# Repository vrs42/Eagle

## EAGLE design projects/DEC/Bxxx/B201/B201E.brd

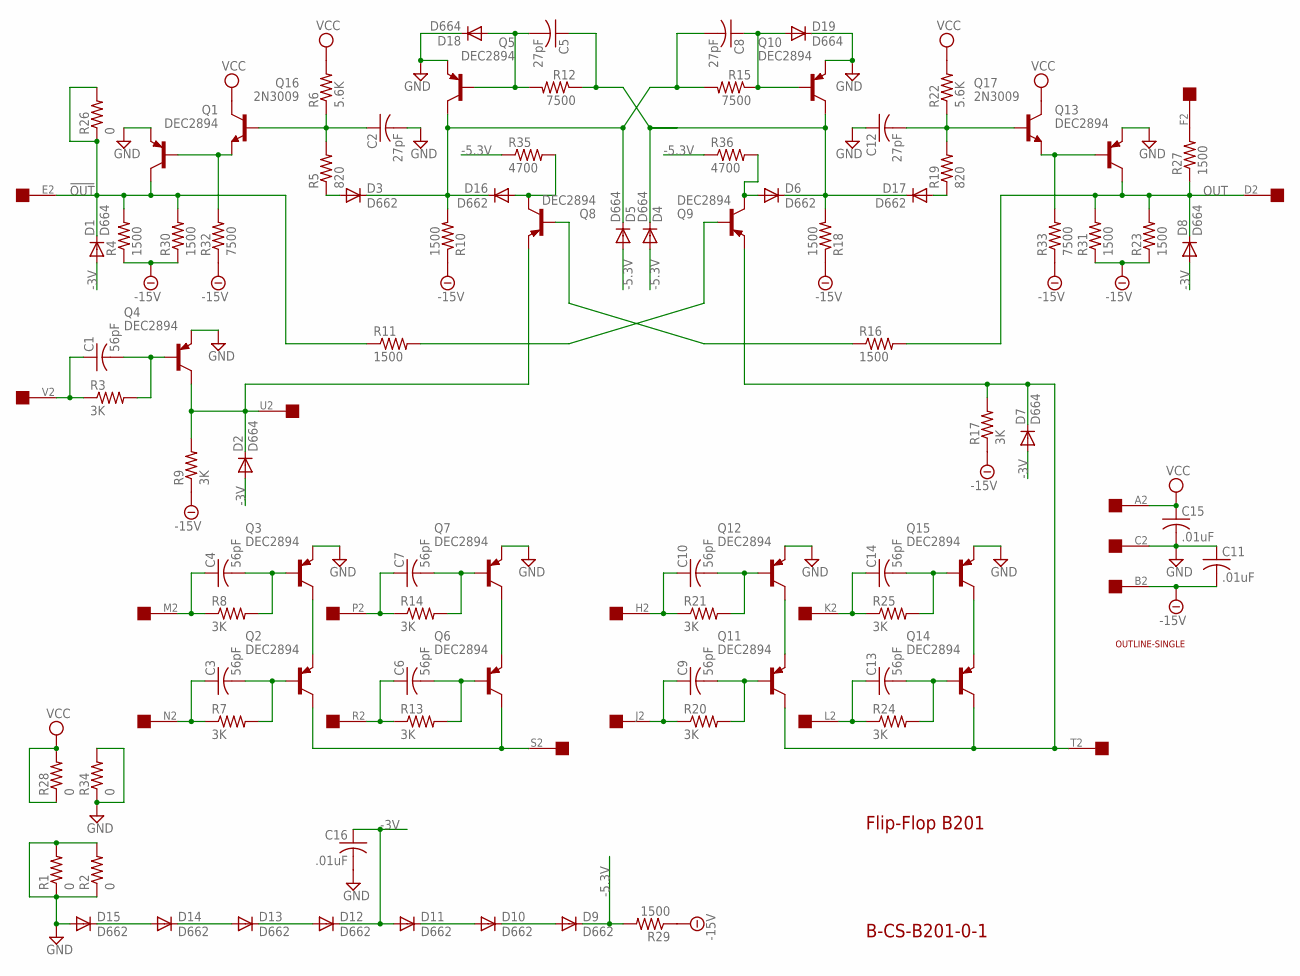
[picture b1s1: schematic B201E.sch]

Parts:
C1, C3, C4, C6, C7, C9, C10, C13, C14: 56pF; C063-025X075
C2, C5, C8, C12: 27pF; C063-025X075
C11, C15, C16: .01uF; C063-025X075
D1, D2, D4, D5, D7, D8, D18, D19: D664; DO35-10
D3, D6, D9, D10, D11, D12, D13, D14, D15, D16, D17: D662; DO35-10
Q1, Q2, Q3, Q4, Q5, Q6, Q7, Q8, Q9, Q10, Q11, Q12, Q13, Q14, Q15: DEC2894; TO5
Q16, Q17: 2N3009; TO5
R1, R2, R26, R28, R34: 0; 0207/10
R3, R7, R8, R9, R13, R14, R17, R20, R21, R24, R25: 3K; 0207/10
R4, R10, R11, R16, R18, R23, R27, R29, R30, R31: 1500; 0207/10
R5, R19: 820; 0207/10
R6, R22: 5.6K; 0207/10
R12, R15, R32, R33: 7500; 0207/10
R35, R36: 4700; 0207/10
U$1: OUTLINE-SINGLE; SINGLE
U$2: EDGE-1; EDGE-CON1

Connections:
!OUT: D1.C, Q1.3 (C), R4.2, R11.1, R26.1, R26.2, R30.2, U$2.E2
-3V: C16.1, D1.A, D2.A, D7.A, D8.A, D11.A, D12.C
-5.3V: D4.A, D5.A, D9.C, R29.2, R35.1, R36.1
-15V: C11.2, R4.1, R9.1, R10.1, R17.1, R18.1, R23.1, R29.1, R30.1, R31.1, R32.1, R33.1, U$2.B2
-.75V: D14.A, D15.C
GND: C2.2, C11.1, C12.1, C15.2, C16.2, D15.A, D18.C, D19.C, Q1.1 (E), Q3.1 (E), Q4.1 (E), Q5.1 (E), Q7.1 (E), Q10.1 (E), Q12.1 (E), Q13.1 (E), Q15.1 (E), R1.1, R1.2, R2.1, R2.2, R34.1, R34.2, U$2.C2
unnamed: C4.1, R8.1, U$2.M2
unnamed: C4.2, Q3.2 (B), R8.2
unnamed: C3.1, R7.1, U$2.N2
unnamed: C3.2, Q2.2 (B), R7.2
unnamed: Q2.1 (E), Q3.3 (C)
unnamed: Q2.3 (C), Q6.3 (C), U$2.S2
unnamed: C7.1, R14.1, U$2.P2
unnamed: C7.2, Q7.2 (B), R14.2
unnamed: C6.1, R13.1, U$2.R2
unnamed: C6.2, Q6.2 (B), R13.2
unnamed: Q6.1 (E), Q7.3 (C)
unnamed: C1.1, R3.1, U$2.V2
unnamed: C10.1, R21.1, U$2.H2
unnamed: C10.2, Q12.2 (B), R21.2
unnamed: C9.1, R20.1, U$2.J2
unnamed: C9.2, Q11.2 (B), R20.2
unnamed: Q11.1 (E), Q12.3 (C)
unnamed: D7.C, Q9.1 (E), Q11.3 (C), Q14.3 (C), R17.2, U$2.T2
unnamed: C14.1, R25.1, U$2.K2
unnamed: C14.2, Q15.2 (B), R25.2
unnamed: C13.1, R24.1, U$2.L2
unnamed: C13.2, Q14.2 (B), R24.2
unnamed: Q14.1 (E), Q15.3 (C)
unnamed: C1.2, Q4.2 (B), R3.2
unnamed: R27.2, U$2.F2
unnamed: D2.C, Q4.3 (C), Q8.1 (E), R9.2, U$2.U2
unnamed: Q1.2 (B), Q16.1 (E), R32.2
unnamed: D9.A, D10.C
unnamed: D10.A, D11.C
unnamed: C2.1, Q16.2 (B), R5.2, R6.1
unnamed: D13.A, D14.C
unnamed: D12.A, D13.C
unnamed: D3.A, R5.1
unnamed: C5.1, D4.C, D6.C, D17.C, Q10.3 (C), R12.1, R18.2
unnamed: Q8.2 (B), R16.1
unnamed: C8.1, D19.A, Q10.2 (B), R15.1
unnamed: C8.2, D3.C, D5.C, D16.C, Q5.3 (C), R10.2, R15.2
unnamed: Q9.2 (B), R11.2
unnamed: C5.2, D18.A, Q5.2 (B), R12.2
unnamed: D16.A, Q8.3 (C), R35.2
unnamed: C12.2, Q17.2 (B), R19.2, R22.1
unnamed: D17.A, R19.1
unnamed: Q13.2 (B), Q17.1 (E), R33.2
unnamed: D6.A, Q9.3 (C), R36.2
OUT: D8.C, Q13.3 (C), R16.2, R23.2, R27.1, R31.2, U$2.D2
VCC: C15.1, Q16.3 (C), Q17.3 (C), R6.2, R22.2, R28.1, R28.2, U$2.A2

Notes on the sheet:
Flip-Flop B201
B-CS-B201-0-1

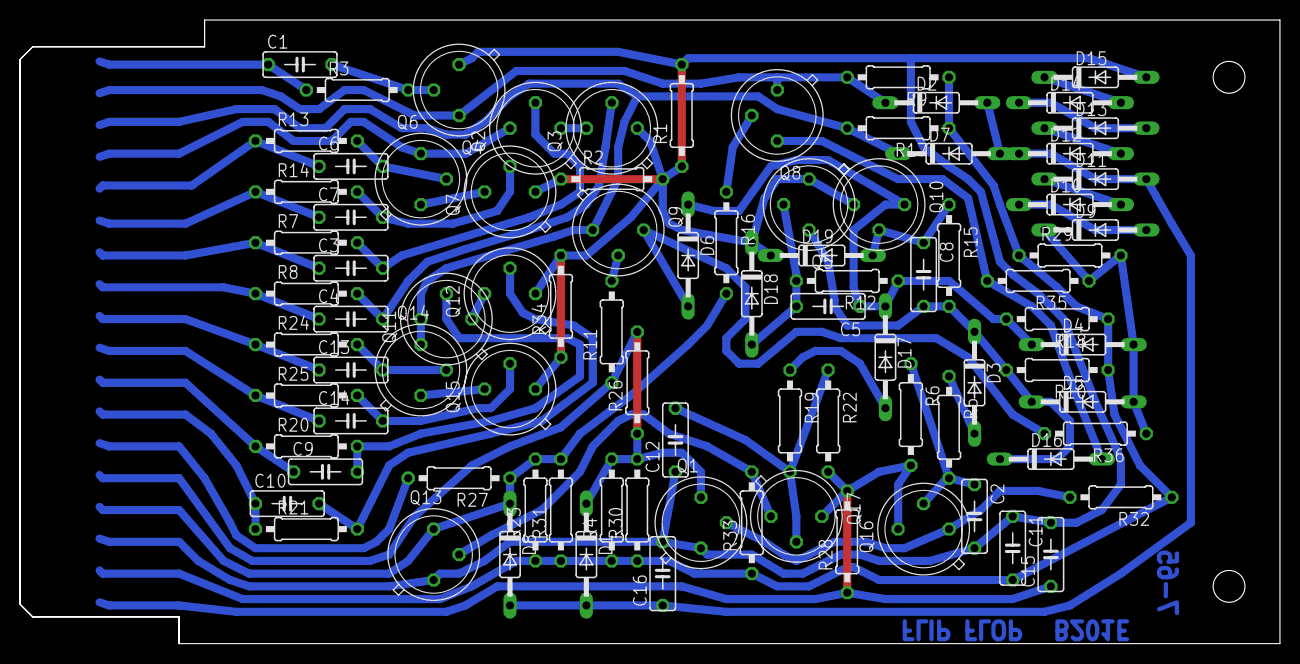
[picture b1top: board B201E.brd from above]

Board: 2 copper layers, 125.7 x 62.2 mm, 90 parts (0 on the bottom side), 52 nets.

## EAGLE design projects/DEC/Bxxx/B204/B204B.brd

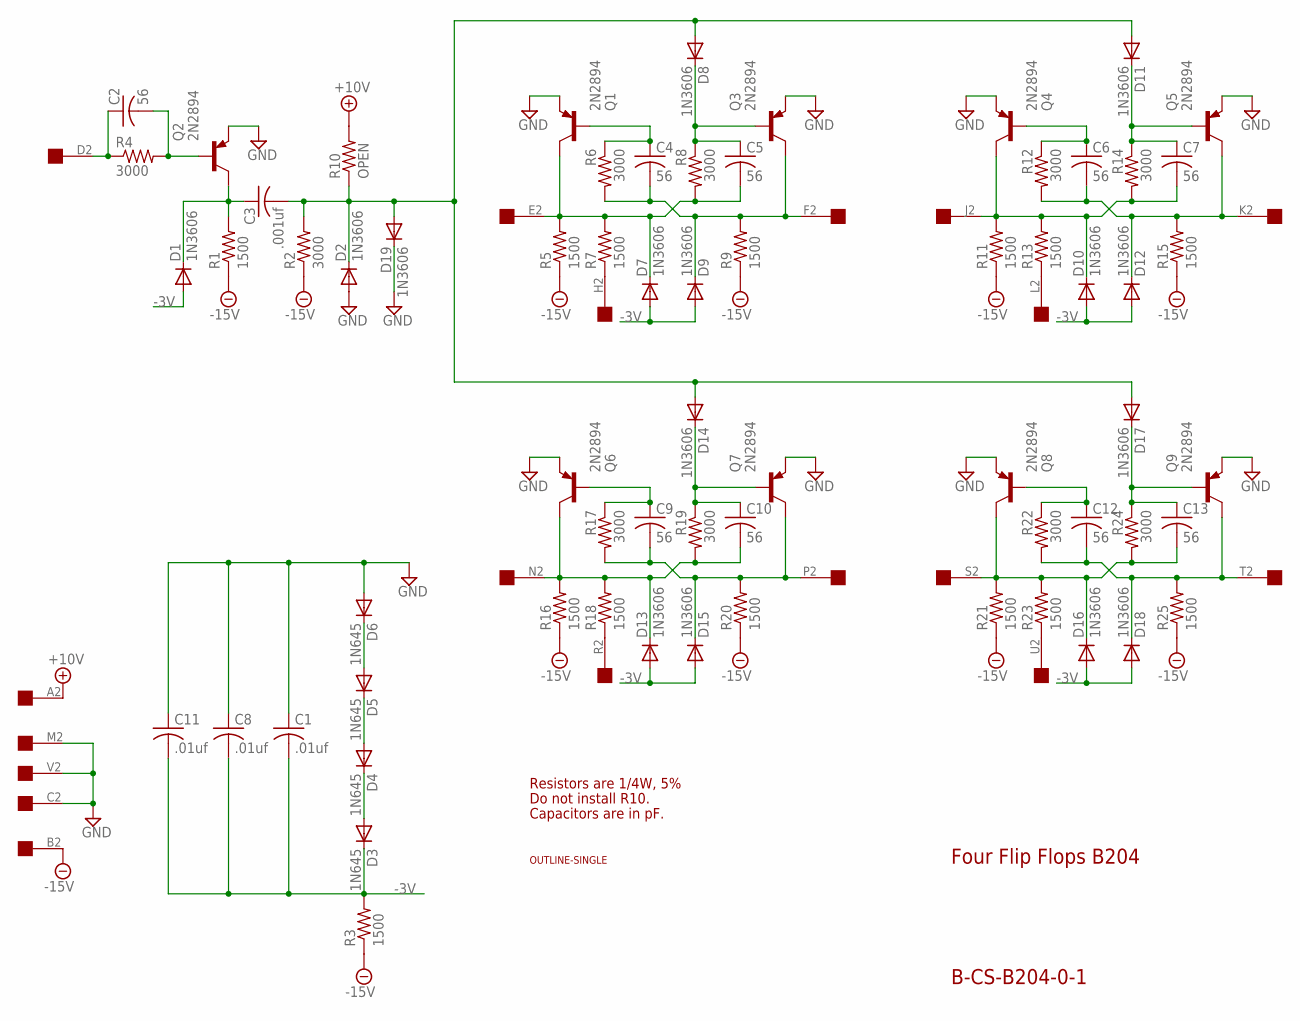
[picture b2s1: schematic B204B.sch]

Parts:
C1, C8, C11: .01uf; C050-025X075
C2, C4, C5, C6, C7, C9, C10, C12, C13: 56; C075-032X103
C3: .001uf; C050-025X075
D1, D2, D7, D8, D9, D10, D11, D12, D13, D14, D15, D16, D17, D18, D19: 1N3606; DO35-10
D3, D4, D5, D6: 1N645; DO35-10
Q1, Q2, Q3, Q4, Q5, Q6, Q7, Q8, Q9: 2N2894; TO39
R1, R3, R5, R7, R9, R11, R13, R15, R16, R18, R20, R21, R23, R25: 1500; 0207/10
R2, R4, R6, R8, R12, R14, R17, R19, R22, R24: 3000; 0207/10
R10: OPEN; 0207/10
U$1: OUTLINE-SINGLE; SINGLE
U$2: EDGE-1; EDGE-CON1

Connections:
+10V: R10.2, U$2.A2
-3V: C1.2, C8.2, C11.2, D1.A, D3.C, D7.A, D9.A, D10.A, D12.A, D13.A, D15.A, D16.A, D18.A, R3.2
-15V: R1.1, R2.1, R3.1, R5.1, R9.1, R11.1, R15.1, R16.1, R20.1, R21.1, R25.1, U$2.B2
GND: C1.1, C8.1, C11.1, D2.A, D6.A, D19.C, Q1.1 (E), Q2.1 (E), Q3.1 (E), Q4.1 (E), Q5.1 (E), Q6.1 (E), Q7.1 (E), Q8.1 (E), Q9.1 (E), U$2.C2, U$2.M2, U$2.V2
unnamed: C2.1, R4.1, U$2.D2
unnamed: C4.1, Q1.2 (B), R6.1
unnamed: C2.2, Q2.2 (B), R4.2
unnamed: C3.1, D1.C, Q2.3 (C), R1.2
unnamed: R7.1, U$2.H2
unnamed: C5.2, D7.C, Q1.3 (C), R5.2, R7.2, R8.2, U$2.E2
unnamed: C5.1, D8.C, Q3.2 (B), R8.1
unnamed: C3.2, D2.C, D8.A, D11.A, D14.A, D17.A, D19.A, R2.2, R10.1
unnamed: C4.2, D9.C, Q3.3 (C), R6.2, R9.2, U$2.F2
unnamed: R13.1, U$2.L2
unnamed: C6.1, Q4.2 (B), R12.1
unnamed: D4.A, D5.C
unnamed: C7.1, D11.C, Q5.2 (B), R14.1
unnamed: C7.2, D10.C, Q4.3 (C), R11.2, R13.2, R14.2, U$2.J2
unnamed: D3.A, D4.C
unnamed: C6.2, D12.C, Q5.3 (C), R12.2, R15.2, U$2.K2
unnamed: R18.1, U$2.R2
unnamed: C9.1, Q6.2 (B), R17.1
unnamed: C10.1, D14.C, Q7.2 (B), R19.1
unnamed: C10.2, D13.C, Q6.3 (C), R16.2, R18.2, R19.2, U$2.N2
unnamed: C9.2, D15.C, Q7.3 (C), R17.2, R20.2, U$2.P2
unnamed: R23.1, U$2.U2
unnamed: C12.1, Q8.2 (B), R22.1
unnamed: C13.1, D17.C, Q9.2 (B), R24.1
unnamed: C13.2, D16.C, Q8.3 (C), R21.2, R23.2, R24.2, U$2.S2
unnamed: C12.2, D18.C, Q9.3 (C), R22.2, R25.2, U$2.T2
unnamed: D5.A, D6.C

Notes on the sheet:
Four Flip Flops B204
B-CS-B204-0-1
Resistors are 1/4W, 5%
Do not install R10.
Capacitors are in pF.

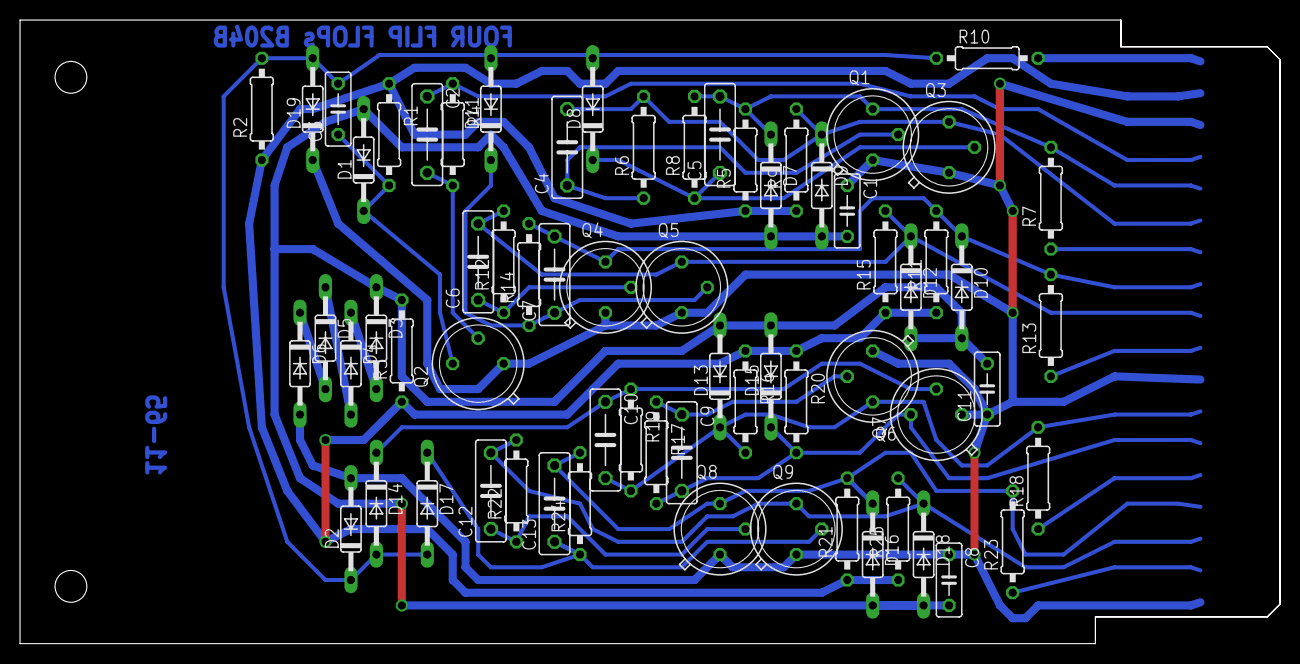
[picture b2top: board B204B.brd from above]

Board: 2 copper layers, 125.7 x 62.2 mm, 68 parts (0 on the bottom side), 31 nets.

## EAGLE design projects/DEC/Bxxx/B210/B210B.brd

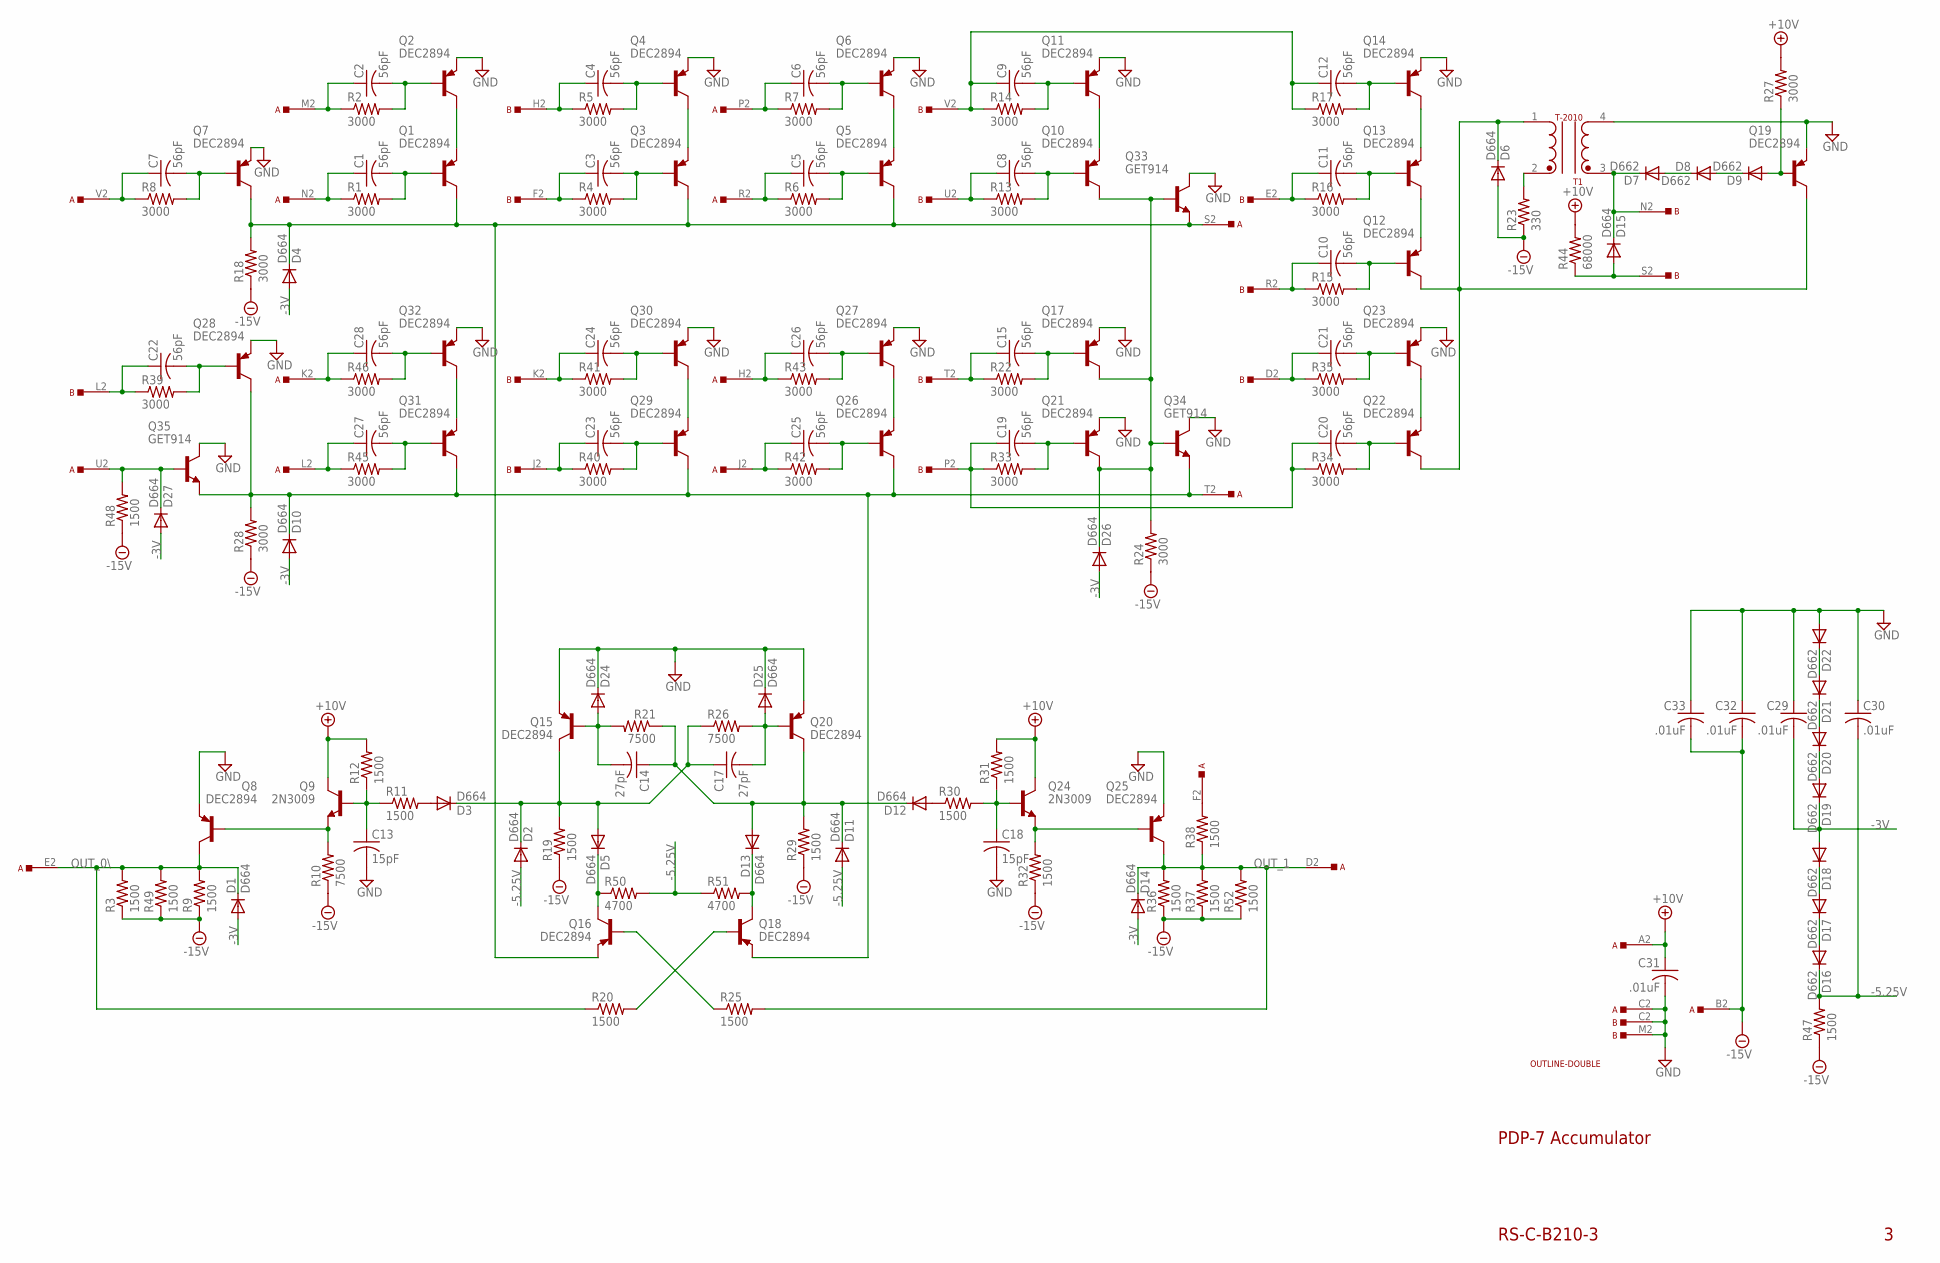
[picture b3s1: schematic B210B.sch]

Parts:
A: SS-TOP; EDGE-CON1
B: SS-TOP; EDGE-CON1
C1, C2, C3, C4, C5, C6, C7, C8, C9, C10, C11, C12, C15, C19, C20, C21, C22, C23, C24, C25, C26, C27, C28: 56pF; C063-025X075
C13, C18: 15pF; C063-025X075
C14, C17: 27pF; C063-025X075
C29, C30, C31, C32, C33: .01uF; C063-025X075
D1, D2, D3, D4, D5, D6, D10, D11, D12, D13, D14, D15, D24, D25, D26, D27: D664; DO35-10
D7, D8, D9, D16, D17, D18, D19, D20, D21, D22: D662; DO35-10
Q1, Q2, Q3, Q4, Q5, Q6, Q7, Q8, Q10, Q11, Q12, Q13, Q14, Q15, Q16, Q17, Q18, Q19, Q20, Q21, Q22, Q23, Q25, Q26, Q27, Q28, Q29, Q30, Q31, Q32: DEC2894; TO5
Q9, Q24: 2N3009; TO5
Q33, Q34, Q35: GET914; TO5
R1, R2, R4, R5, R6, R7, R8, R13, R14, R15, R16, R17, R18, R22, R24, R27, R28, R33, R34, R35, R39, R40, R41, R42, R43, R45, R46: 3000; 0207/10
R3, R9, R11, R12, R19, R20, R25, R29, R30, R31, R32, R36, R37, R38, R47, R48, R49, R52: 1500; 0207/10
R10, R21, R26: 7500; 0207/10
R23: 330; 0207/10
R44: 68000; 0207/10
R50, R51: 4700; 0207/10
T1: T-2010; TRANSFORMER2
U$1: OUTLINE-DOUBLE; DOUBLE

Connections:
+10V: A.A2, C31.1, Q9.3 (C), Q24.3 (C), R12.2, R27.2, R31.2, R44.2
-3V: C29.2, D1.A, D4.A, D10.A, D14.A, D18.A, D19.C, D26.A, D27.A
-5.25V: C30.2, D2.A, D11.A, D16.C, R47.2, R50.2, R51.1
-15V: A.B2, C32.2, C33.2, D6.A, R3.1, R9.1, R10.1, R18.1, R19.1, R23.1, R24.1, R28.1, R29.1, R32.1, R36.1, R37.1, R47.1, R48.1, R49.1, R52.1
GND: A.C2, B.C2, B.M2, C13.2, C18.2, C29.1, C30.1, C31.2, C32.1, C33.1, D22.A, D24.C, D25.C, Q2.1 (E), Q4.1 (E), Q6.1 (E), Q7.1 (E), Q8.1 (E), Q11.1 (E), Q14.1 (E), Q15.1 (E), Q17.1 (E), Q19.1 (E), Q20.1 (E), Q21.1 (E), Q23.1 (E), Q25.1 (E), Q27.1 (E), Q28.1 (E), Q30.1 (E), Q32.1 (E), Q33.3 (C), Q34.3 (C), Q35.3 (C), T1.4
unnamed: A.N2, C1.1, R1.1
unnamed: C1.2, Q1.2 (B), R1.2
unnamed: A.M2, C2.1, R2.1
unnamed: C2.2, Q2.2 (B), R2.2
unnamed: B.F2, C3.1, R4.1
unnamed: C3.2, Q3.2 (B), R4.2
unnamed: B.H2, C4.1, R5.1
unnamed: C4.2, Q4.2 (B), R5.2
unnamed: A.R2, C5.1, R6.1
unnamed: C5.2, Q5.2 (B), R6.2
unnamed: A.P2, C6.1, R7.1
unnamed: C6.2, Q6.2 (B), R7.2
unnamed: A.V2, C7.1, R8.1
unnamed: C7.2, Q7.2 (B), R8.2
unnamed: D6.C, Q12.3 (C), Q19.3 (C), Q22.3 (C), T1.1
unnamed: R23.2, T1.2
unnamed: Q10.1 (E), Q11.3 (C)
unnamed: D26.C, Q10.3 (C), Q17.3 (C), Q21.3 (C), Q33.2 (B), Q34.2 (B), R24.2
unnamed: B.U2, C8.1, R13.1
unnamed: C8.2, Q10.2 (B), R13.2
unnamed: B.V2, C9.1, C12.1, R14.1, R17.1
unnamed: C9.2, Q11.2 (B), R14.2
unnamed: B.R2, C10.1, R15.1
unnamed: C10.2, Q12.2 (B), R15.2
unnamed: B.E2, C11.1, R16.1
unnamed: C11.2, Q13.2 (B), R16.2
unnamed: B.N2, D7.C, D15.C, T1.3
unnamed: C12.2, Q14.2 (B), R17.2
unnamed: B.T2, C15.1, R22.1
unnamed: C15.2, Q17.2 (B), R22.2
unnamed: C17.1, D2.C, D3.C, D5.A, Q15.3 (C), R19.2, R26.1
unnamed: C17.2, D25.A, Q20.2 (B), R26.2
unnamed: Q16.2 (B), R25.1
unnamed: Q18.2 (B), R20.2
unnamed: C14.1, D11.C, D12.C, D13.A, Q20.3 (C), R21.1, R29.2
unnamed: C14.2, D24.A, Q15.2 (B), R21.2
unnamed: B.P2, C19.1, C20.1, R33.1, R34.1
unnamed: C19.2, Q21.2 (B), R33.2
unnamed: D7.A, D8.C
unnamed: D8.A, D9.C
unnamed: D9.A, Q19.2 (B), R27.1
unnamed: D21.A, D22.C
unnamed: B.L2, C22.1, R39.1
unnamed: C22.2, Q28.2 (B), R39.2
unnamed: A.T2, D10.C, Q18.1 (E), Q26.3 (C), Q28.3 (C), Q29.3 (C), Q31.3 (C), Q34.1 (E), Q35.1 (E), R28.2
unnamed: D5.C, Q16.3 (C), R50.1
unnamed: B.S2, D15.A, R44.1
unnamed: C25.2, Q26.2 (B), R42.2
unnamed: Q1.1 (E), Q2.3 (C)
unnamed: A.S2, D4.C, Q1.3 (C), Q3.3 (C), Q5.3 (C), Q7.3 (C), Q16.1 (E), Q33.1 (E), R18.2
unnamed: Q5.1 (E), Q6.3 (C)
unnamed: Q3.1 (E), Q4.3 (C)
unnamed: Q12.1 (E), Q13.3 (C)
unnamed: Q13.1 (E), Q14.3 (C)
unnamed: A.L2, C27.1, R45.1
unnamed: C27.2, Q31.2 (B), R45.2
unnamed: A.K2, C28.1, R46.1
unnamed: C28.2, Q32.2 (B), R46.2
unnamed: C20.2, Q22.2 (B), R34.2
unnamed: Q31.1 (E), Q32.3 (C)
unnamed: A.H2, C26.1, R43.1
unnamed: C26.2, Q27.2 (B), R43.2
unnamed: C23.2, Q29.2 (B), R40.2
unnamed: Q26.1 (E), Q27.3 (C)
unnamed: A.J2, C25.1, R42.1
unnamed: B.K2, C24.1, R41.1
unnamed: C24.2, Q30.2 (B), R41.2
unnamed: B.D2, C21.1, R35.1
unnamed: Q29.1 (E), Q30.3 (C)
unnamed: B.J2, C23.1, R40.1
unnamed: C21.2, Q23.2 (B), R35.2
unnamed: Q22.1 (E), Q23.3 (C)
unnamed: D20.A, D21.C
unnamed: D19.A, D20.C
unnamed: D16.A, D17.C
unnamed: D17.A, D18.C
unnamed: D13.C, Q18.3 (C), R51.2
unnamed: D3.A, R11.2
unnamed: C13.1, Q9.2 (B), R11.1, R12.1
unnamed: C18.1, Q24.2 (B), R30.2, R31.1
unnamed: D12.A, R30.1
unnamed: Q8.2 (B), Q9.1 (E), R10.2
unnamed: Q24.1 (E), Q25.2 (B), R32.2
unnamed: A.F2, R38.2
unnamed: A.U2, D27.C, Q35.2 (B), R48.2
OUT_0\: A.E2, D1.C, Q8.3 (C), R3.2, R9.2, R20.1, R49.2
OUT_1: A.D2, D14.C, Q25.3 (C), R25.2, R36.2, R37.2, R38.1, R52.2

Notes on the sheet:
RS-C-B210-3
PDP-7 Accumulator

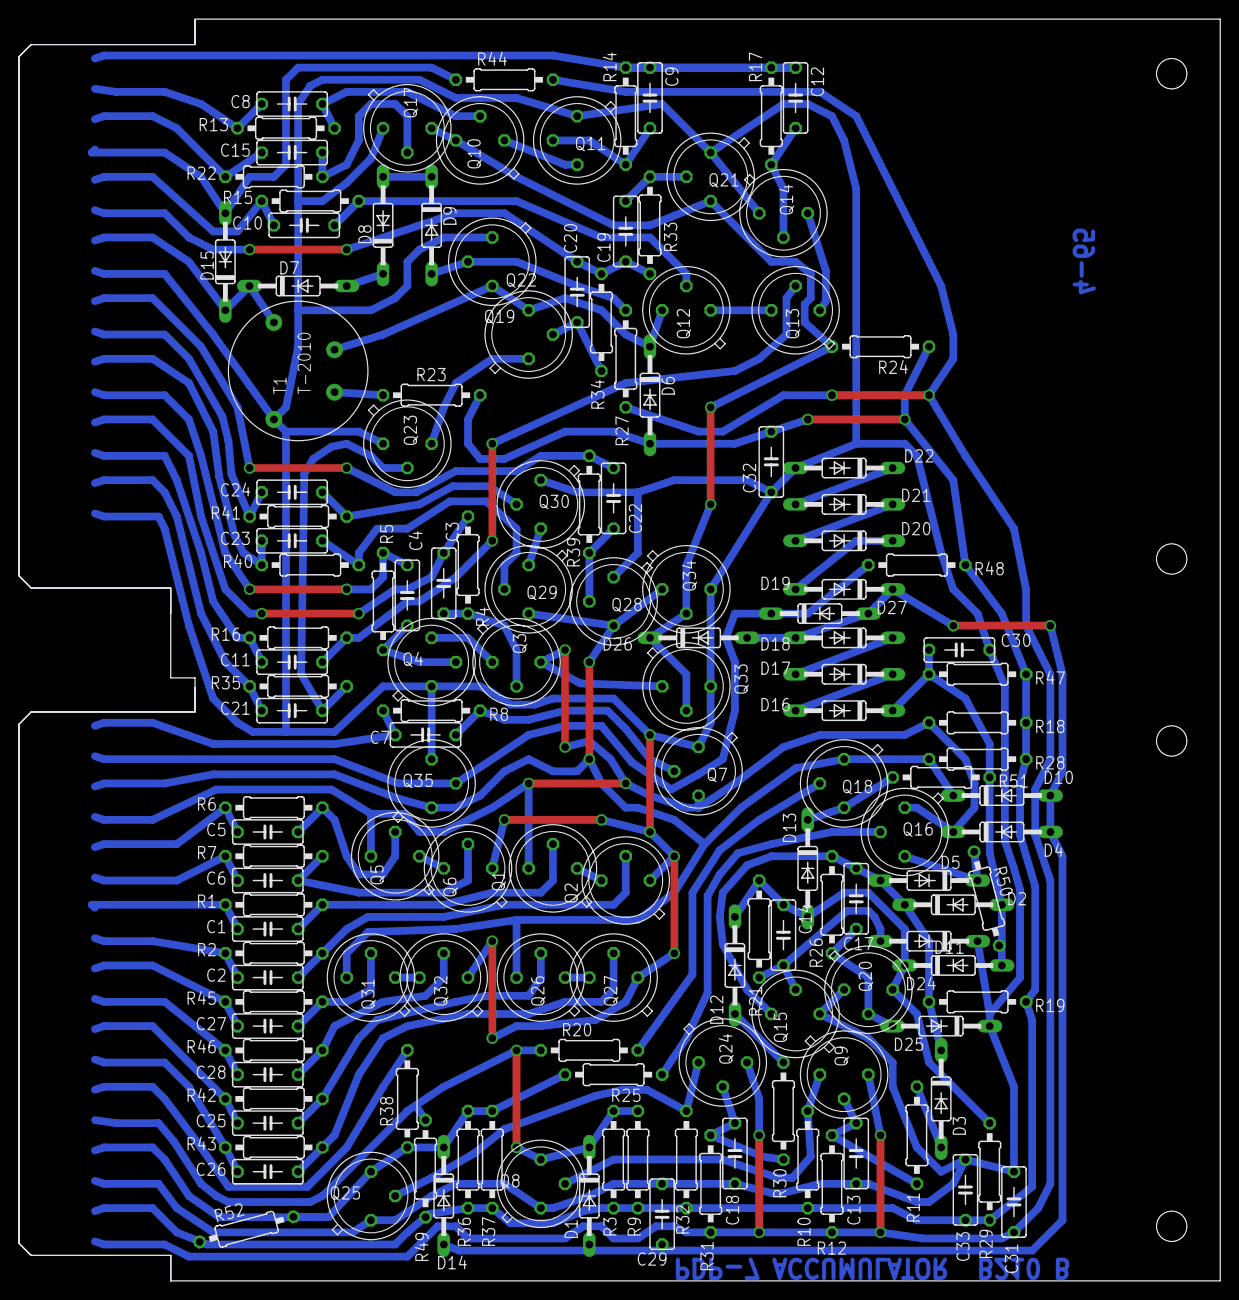
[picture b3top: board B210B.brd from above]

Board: 2 copper layers, 125.7 x 132.1 mm, 149 parts (0 on the bottom side), 92 nets.

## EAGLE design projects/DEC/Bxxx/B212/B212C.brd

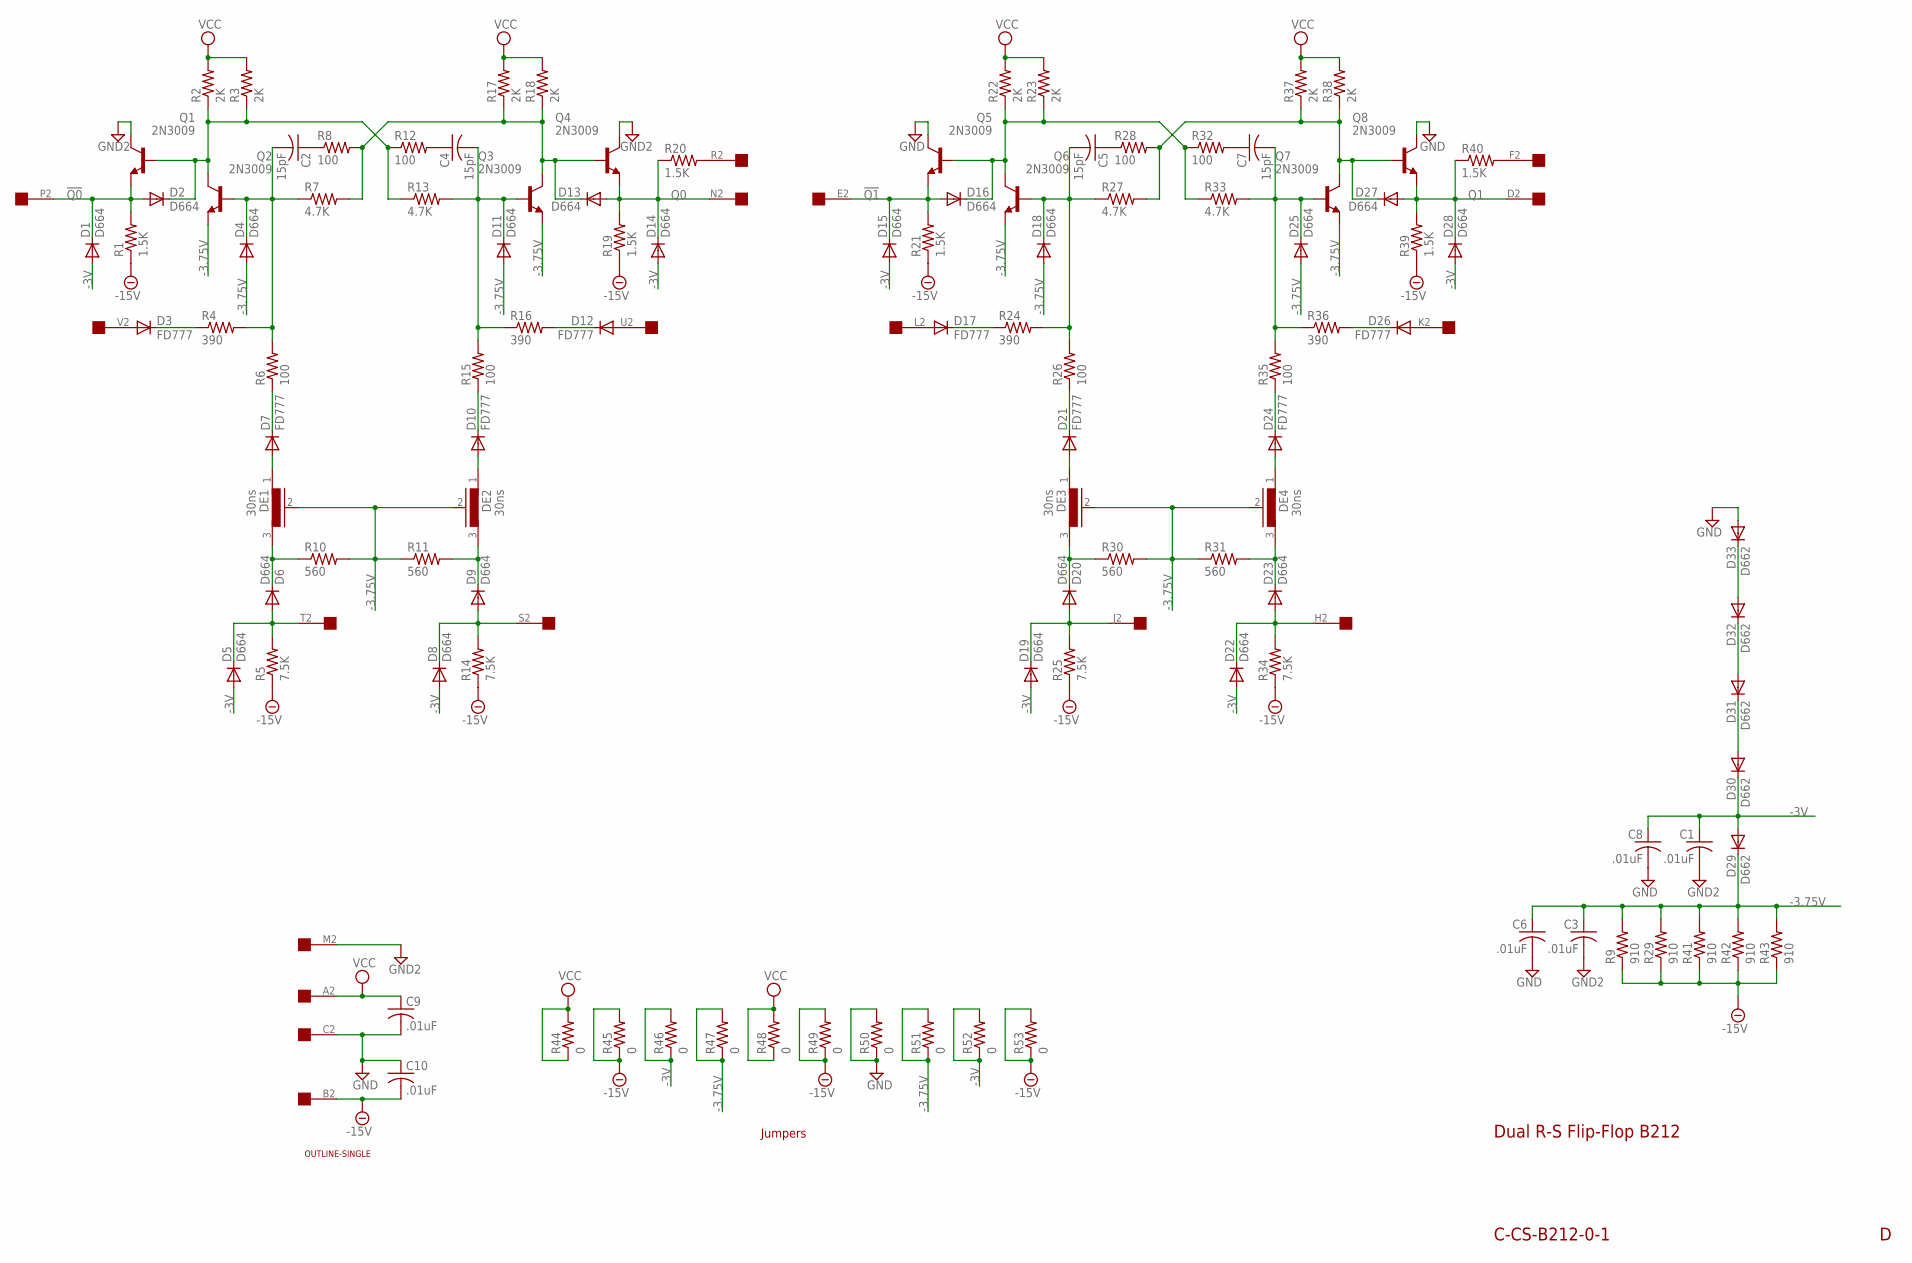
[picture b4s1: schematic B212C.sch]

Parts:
C1, C3, C6, C8, C9, C10: .01uF; C063-025X075
C2, C5, C7: 15pF; C063-025X075
C4: 15pF; C050-025X075
D1, D2, D4, D5, D6, D8, D9, D11, D13, D14, D15, D16, D18, D19, D20, D22, D23, D25, D27, D28: D664; DO35-10
D3, D7, D10, D12, D17, D21, D24, D26: FD777; DO35-10
D29, D30, D31, D32, D33: D662; DO35-10
DE1, DE2, DE3, DE4: 30ns; RCL-L-00-05
Q1, Q2, Q3, Q4, Q5, Q6, Q7, Q8: 2N3009; TO5
R1, R19, R20, R21, R39, R40: 1.5K; 0207/10
R2, R3, R17, R18, R22, R23, R37, R38: 2K; 0207/10
R4, R16, R24, R36: 390; 0207/10
R5, R14, R25, R34: 7.5K; 0207/10
R6, R8, R12, R15, R26, R28, R32, R35: 100; 0207/10
R7, R13, R27, R33: 4.7K; 0207/10
R9, R29, R41, R42, R43: 910; 0207/10
R10, R11, R30, R31: 560; 0207/10
R44, R45, R46, R47, R48, R49, R50, R51, R52, R53: 0; 0207/10
U$1: OUTLINE-SINGLE; SINGLE
U$2: EDGE-1; EDGE-CON1

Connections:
!Q0: D1.C, D2.A, Q1.1 (E), R1.2, U$2.P2
!Q1: D15.C, D16.A, Q5.1 (E), R21.2, U$2.E2
-3.75V: C3.1, C6.1, D4.A, D11.A, D18.A, D25.A, D29.C, DE1.2, DE2.2, DE3.2, DE4.2, Q2.1 (E), Q3.1 (E), Q6.1 (E), Q7.1 (E), R9.2, R10.2, R11.1, R29.2, R30.2, R31.1, R41.2, R42.2, R43.2, R47.1, R47.2, R51.1, R51.2
-3V: C1.1, C8.1, D1.A, D5.A, D8.A, D14.A, D15.A, D19.A, D22.A, D28.A, D29.A, D30.C, R46.1, R46.2, R52.1, R52.2
-15V: C10.2, R1.1, R5.1, R9.1, R14.1, R19.1, R21.1, R25.1, R29.1, R34.1, R39.1, R41.1, R42.1, R43.1, R45.1, R45.2, R49.1, R49.2, R53.1, R53.2, U$2.B2
GND: C6.2, C8.2, C9.2, C10.1, D33.A, Q5.3 (C), Q8.3 (C), R50.1, R50.2, U$2.C2
GND2: C1.2, C3.2, Q1.3 (C), Q4.3 (C), U$2.M2
unnamed: C2.1, R8.1
unnamed: C2.2, D4.C, Q2.2 (B), R4.2, R6.2, R7.1
unnamed: D13.C, Q3.3 (C), Q4.2 (B), R7.2, R8.2, R17.1, R18.1
unnamed: D2.C, Q1.2 (B), Q2.3 (C), R2.1, R3.1, R12.1, R13.1
unnamed: D3.C, R4.1
unnamed: D30.A, D31.C
unnamed: D31.A, D32.C
unnamed: D32.A, D33.C
unnamed: D3.A, U$2.V2
unnamed: D7.C, R6.1
unnamed: D7.A, DE1.1
unnamed: D9.C, DE2.3, R11.2
unnamed: D6.C, DE1.3, R10.1
unnamed: D5.C, D6.A, R5.2, U$2.T2
unnamed: C4.1, R12.2
unnamed: C4.2, D11.C, Q3.2 (B), R13.2, R15.2, R16.1
unnamed: D10.A, DE2.1
unnamed: D10.C, R15.1
unnamed: D12.A, U$2.U2
unnamed: D12.C, R16.2
unnamed: R20.2, U$2.R2
unnamed: D8.C, D9.A, R14.2, U$2.S2
unnamed: D16.C, Q5.2 (B), Q6.3 (C), R22.1, R23.1, R32.1, R33.1
unnamed: D26.C, R36.2
unnamed: C5.2, D18.C, Q6.2 (B), R24.2, R26.2, R27.1
unnamed: D17.A, U$2.L2
unnamed: D17.C, R24.1
unnamed: D21.A, DE3.1
unnamed: D21.C, R26.1
unnamed: D19.C, D20.A, R25.2, U$2.J2
unnamed: C5.1, R28.1
unnamed: D27.C, Q7.3 (C), Q8.2 (B), R27.2, R28.2, R37.1, R38.1
unnamed: C7.1, R32.2
unnamed: C7.2, D25.C, Q7.2 (B), R33.2, R35.2, R36.1
unnamed: R40.2, U$2.F2
unnamed: D26.A, U$2.K2
unnamed: D24.A, DE4.1
unnamed: D24.C, R35.1
unnamed: D20.C, DE3.3, R30.1
unnamed: D23.C, DE4.3, R31.2
unnamed: D22.C, D23.A, R34.2, U$2.H2
Q0: D13.A, D14.C, Q4.1 (E), R19.2, R20.1, U$2.N2
Q1: D27.A, D28.C, Q8.1 (E), R39.2, R40.1, U$2.D2
VCC: C9.1, R2.2, R3.2, R17.2, R18.2, R22.2, R23.2, R37.2, R38.2, R44.1, R44.2, R48.1, R48.2, U$2.A2

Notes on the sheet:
Dual R-S Flip-Flop B212
C-CS-B212-0-1
Jumpers

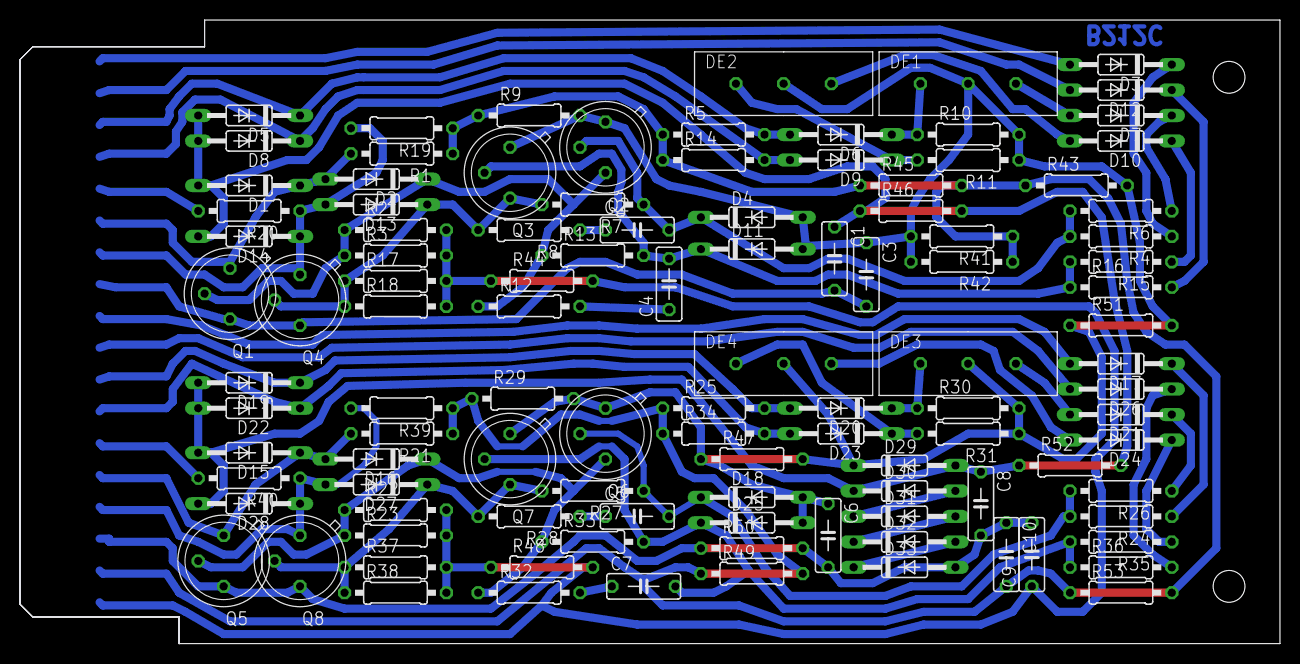
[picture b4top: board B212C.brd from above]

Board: 2 copper layers, 125.7 x 62.2 mm, 110 parts (0 on the bottom side), 51 nets.
